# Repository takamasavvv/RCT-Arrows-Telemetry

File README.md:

# RCT-Arrows-Telemetry
Telemetry module for GS-8

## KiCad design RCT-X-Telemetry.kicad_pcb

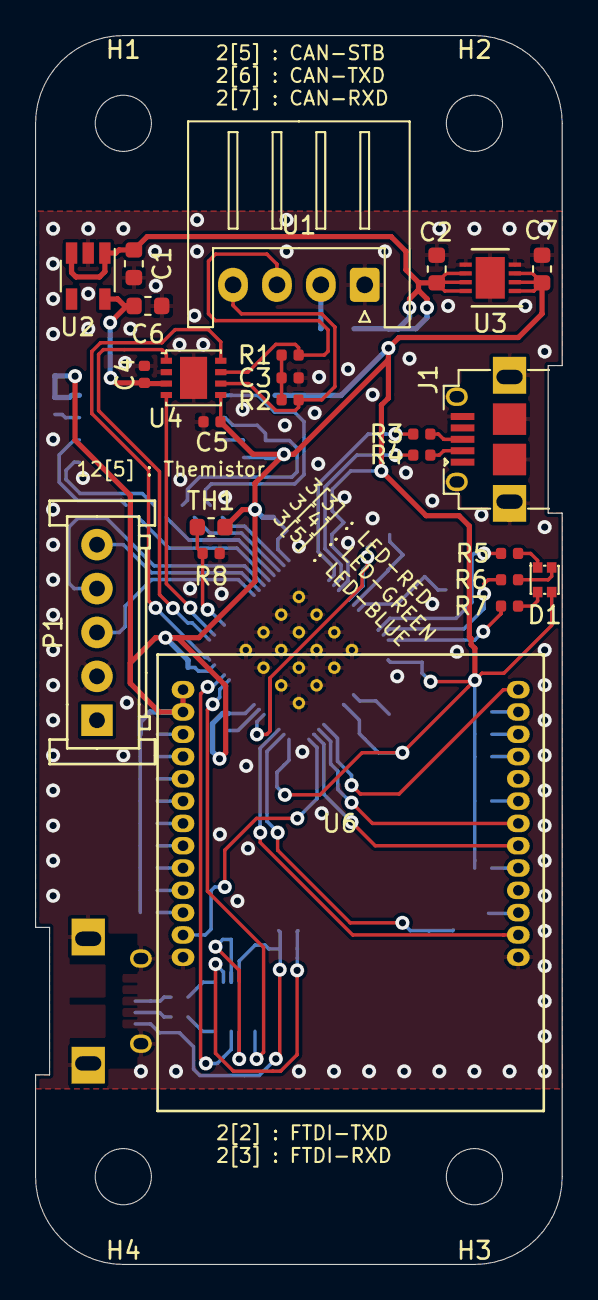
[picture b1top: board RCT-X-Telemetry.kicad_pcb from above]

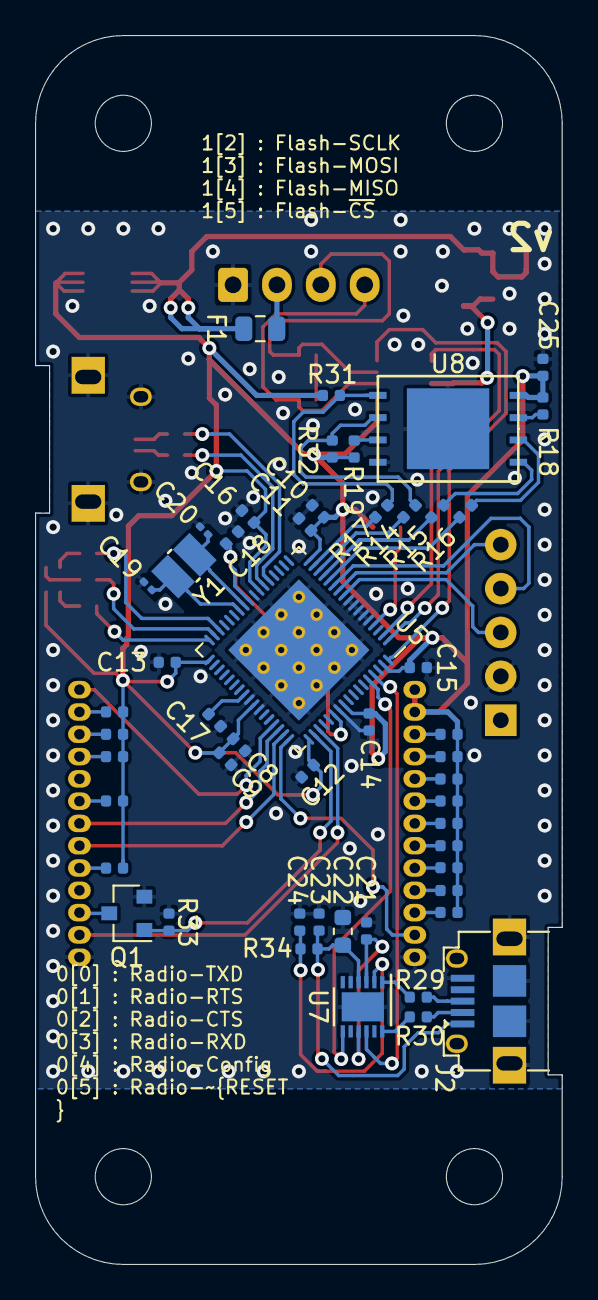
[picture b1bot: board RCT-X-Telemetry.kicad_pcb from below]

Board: 2 copper layers, 30.0 x 70.0 mm, 79 parts (51 on the bottom side), 69 nets.

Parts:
C1, C2, C6, C7, C22: 10uF; C_0603_1608Metric
C3: 4.7nF; C_0402_1005Metric
C4, C5, C8, C9, C10, C11, C12, C13, C15, C21, C23, C24, C25: 0.1uF; C_0402_1005Metric
C14, C16, C17, C18: 1uF; C_0402_1005Metric
C19, C20: 9pF; C_0201_0603Metric
D1: LED_RGBA; LED_LiteOn_LTST-C19HE1WT
F1: Polyfuse; Fuse_0805_2012Metric
H1, H2, H3, H4: MountingHole; MountingHole_3.2mm_M3
J1, J2: USB_B_Micro; Hirose_ZX_ZX62D-B-5P8
P1: KRC_Conn_SWD; JST_JQ_05JQ-BT_1x05_P2.5mm_Vertical
Q1: Q_NMOS_DGS; SOT-23
R1, R2: 56Ω; R_0402_1005Metric
R3, R4, R14, R15, R16, R17, R29, R30: 22Ω; R_0402_1005Metric
R5: 1.5kΩ; R_0402_1005Metric
R6, R7: 820Ω; R_0402_1005Metric
R8: 1MΩ; R_0402_1005Metric
R9, R10, R11, R12, R13, R20, R21, R22, R23, R24, R25, R26, R27, R28: 47kΩ; R_0402_1005Metric
R18, R19, R31, R32: 4.7kΩ; R_0402_1005Metric
R33: 10kΩ; R_0402_1005Metric
R34: 1kΩ; R_0402_1005Metric
TH1: Thermistor_NTC; R_0603_1608Metric
U1: KRC_Conn_CAN; JST_XH_S4B-XH-A_1x04_P2.50mm_Horizontal
U2: LT1761-5; TSOT-23-5
U3: LT1965xDD-3.3; DFN-8-1EP_3x3mm_P0.5mm_EP1.66x2.38mm
U4: NCV7342; DFN-8-1EP_3x3mm_P0.65mm_EP1.55x2.4mm
U5: CY8C58xxLTI-LPxxx; Cypress_QFN-68_EP_8x8_Pitch0.4mm
U6: RM-92X; RFLink_Module_RM-92A
U7: FT234XD; DFN-12-1EP_3x3mm_P0.45mm_EP1.66x2.38mm
U8: W25N01GVxxIG-IT; WSON-8_8x6mm_P1.27mm
Y1: Crystal_MHz; Crystal_Murata_XRCHA

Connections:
+3V3: C5.1, C7.1, C8.1, C9.1, C10.1, C11.1, C12.1, C13.1, C14.1, C15.1, C16.1, C25.1, D1.4, R9.2, R10.2, R11.2, R12.2, R13.2, R18.1, R19.1, R20.1, R21.1, R22.1, R23.1, R24.1, R25.1, R26.1, R27.1, R28.1, R31.1, R32.1, TH1.1, U3.1, U3.2, U3.3, U4.5, U5.17, U5.24, U5.35, U5.44, U5.52, U5.59, U5.67, U6.14, U6.15, U8.8
+5V: C4.2, C6.1, U2.5, U4.3
/CAN-RXD: U4.4, U5.2
/CAN-STB: U4.8, U5.68
/CAN-TXD: U4.1, U5.1
/FTDI-RXD: U5.65, U7.10
/FTDI-TXD: U5.64, U7.7
/FTDI-~RESET: C24.1, R34.2, U7.2
/Flash-MISO: R14.2, U5.15
/Flash-MOSI: R15.2, U5.14
/Flash-SCLK: R16.2, U5.13
/Flash-~CS: R17.2, U5.16
/Radio-CTS: U5.50, U6.6
/Radio-Config: Q1.1, R33.1, U5.53
/Radio-RTS: U5.49, U6.7
/Radio-RXD: U5.51, U6.25
/Radio-TXD: U5.48, U6.13
/Radio-~RESET: U5.54, U6.2
GND: C1.2, C2.2, C3.2, C4.1, C5.2, C6.2, C7.2, C8.2, C9.2, C10.2, C11.2, C12.2, C13.2, C14.2, C15.2, C16.2, C17.1, C18.1, C19.2, C20.2, C21.2, C22.2, C23.2, C24.2, C25.2, J1.5, J2.5, P1.2, Q1.2, R8.2, R33.2, U1.1, U2.2, U3.4, U3.5, U3.9, U4.2, U4.9, U5.5, U5.6, U5.7, U5.8, U5.9, U5.25, U5.43, U5.45, U5.58, U5.69, U6.1, U6.26, U7.5, U7.13, U8.4, U8.9
unnamed: C1.1, C2.1, F1.1, U2.1, U2.3, U3.6, U3.7, U3.8
unnamed: C3.1, R1.2, R2.1
unnamed: C17.2, U5.42
unnamed: C18.2, U5.26, U5.57
unnamed: C19.1, U5.28, Y1.1
unnamed: C20.1, U5.27, Y1.2
unnamed: C21.1, U7.3, U7.9
unnamed: C22.1, C23.1, J2.1, R34.1, U7.4
unnamed: D1.1, R5.1
unnamed: D1.2, R6.1
unnamed: D1.3, R7.1
unnamed: F1.2, U1.2
unnamed: J1.2, R4.1
unnamed: J1.3, R3.1
unnamed: J2.2, R30.1
unnamed: J2.3, R29.1
unnamed: P1.3, U5.10
unnamed: P1.4, U5.12
unnamed: P1.5, U5.11
unnamed: Q1.3, U6.3
unnamed: R1.1, U1.3, U4.7
unnamed: R2.2, U1.4, U4.6
unnamed: R3.2, U5.22
unnamed: R4.2, U5.23
unnamed: R5.2, U5.32
unnamed: R6.2, U5.33
unnamed: R7.2, U5.34
unnamed: R8.1, TH1.2, U5.4
unnamed: R9.1, U6.20
unnamed: R10.1, U6.21
unnamed: R11.1, U6.22
unnamed: R12.1, U6.23
unnamed: R13.1, U6.24
unnamed: R14.1, R32.2, U8.2
unnamed: R15.1, U8.5
unnamed: R16.1, U8.6
unnamed: R17.1, R31.2, U8.1
unnamed: R18.2, U8.7
unnamed: R19.2, U8.3
unnamed: R20.2, U6.8
unnamed: R21.2, U6.10
unnamed: R22.2, U6.5
unnamed: R23.2, U6.11
unnamed: R24.2, U6.12
unnamed: R25.2, U6.16
unnamed: R26.2, U6.17
unnamed: R27.2, U6.18
unnamed: R28.2, U6.19
unnamed: R29.2, U7.1
unnamed: R30.2, U7.12

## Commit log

2019-09-17 [add]complete v1.0.0
2019-09-20 modified parts placement
2019-09-20 add plot sheets
2019-09-20 add circuit svg link
2019-10-10 Completed Rev2
2019-10-29 rename project
